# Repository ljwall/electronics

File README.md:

# Electronics

Vague notes on my electronics projects.

## Bootstrapping AVR development

Using a borrowed Arduino UNO to build a version of the [metaboard](https://metalab.at/wiki/Metaboard) prototype board and an ISP.

* [Turn an Arduino UNO into an AVRISP, and make an LED blink](./01_arduino_isp_blink/)
* [Mini-metaboard on a breadboard](./02_mini_meta/)
* [AVRProg on breadboard metaboard](./03_meta_avr_prog/)

## Audio

* [lm386 amplifier](./lm386-amp/)

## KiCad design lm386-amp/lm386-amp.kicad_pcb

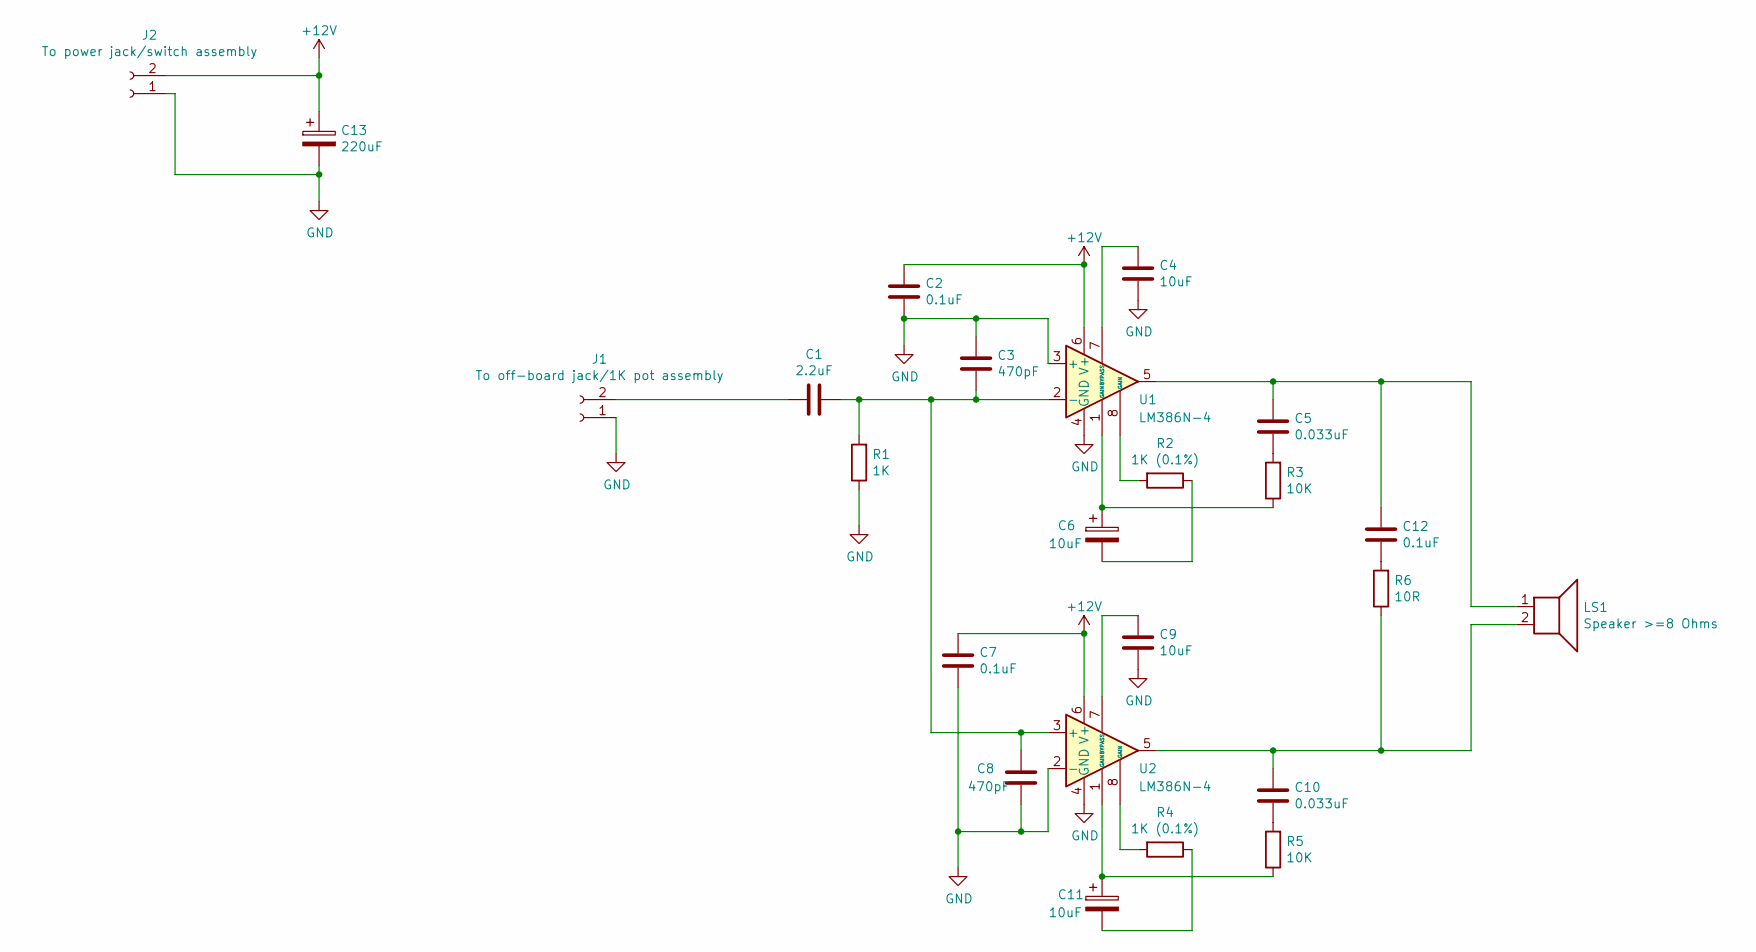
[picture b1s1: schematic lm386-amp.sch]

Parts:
C1: 2.2uF; CP_Radial_D5.0mm_P2.50mm
C2, C7, C12: 0.1uF; C_Disc_D3.4mm_W2.1mm_P2.50mm
C3, C8: 470pF; C_Disc_D3.4mm_W2.1mm_P2.50mm
C4, C6, C9, C11: 10uF; CP_Radial_D6.3mm_P2.50mm
C5, C10: 0.033uF; C_Disc_D4.7mm_W2.5mm_P5.00mm
C13: 220uF; CP_Radial_D8.0mm_P2.50mm
J1: To off-board jack/1K pot assembly; rs-pro-screw-terminal-block-low-prof-P3.5mm-2x1
J2: To power jack/switch assembly; rs-pro-screw-terminal-block-low-prof-P3.5mm-2x1
LS1: Speaker >=8 Ohms; rs-pro-screw-terminal-block-low-prof-P3.5mm-2x1
R1: 1K; R_Axial_DIN0411_L9.9mm_D3.6mm_P12.70mm_Horizontal
R2, R4: 1K (0.1%); R_Axial_DIN0411_L9.9mm_D3.6mm_P12.70mm_Horizontal
R3, R5: 10K; R_Axial_DIN0204_L3.6mm_D1.6mm_P7.62mm_Horizontal
R6: 10R; R_Axial_DIN0204_L3.6mm_D1.6mm_P7.62mm_Horizontal
U1, U2: LM386N-4; DIP-8_W7.62mm_Socket

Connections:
+12V: C2.1, C7.1, C13.1, J2.2, U1.6 (V+), U2.6 (V+)
GND: C2.2, C3.1, C4.2, C7.2, C8.2, C9.2, C13.2, J1.1, J2.1, R1.1, U1.3 (+), U1.4 (GND), U2.2 (-), U2.4 (GND)
unnamed: C1.1, C3.2, C8.1, R1.2, U1.2 (-), U2.3 (+)
unnamed: C1.2, J1.2
unnamed: C4.1, U1.7 (BYPASS)
unnamed: C5.2, R3.2
unnamed: C6.1, R3.1, U1.1 (GAIN)
unnamed: C6.2, R2.1
unnamed: C9.1, U2.7 (BYPASS)
unnamed: C10.1, LS1.2, R6.1, U2.5
unnamed: C10.2, R5.2
unnamed: C11.1, R5.1, U2.1 (GAIN)
unnamed: C11.2, R4.1
unnamed: C5.1, C12.1, LS1.1, U1.5
unnamed: C12.2, R6.2
unnamed: R2.2, U1.8 (GAIN)
unnamed: R4.2, U2.8 (GAIN)

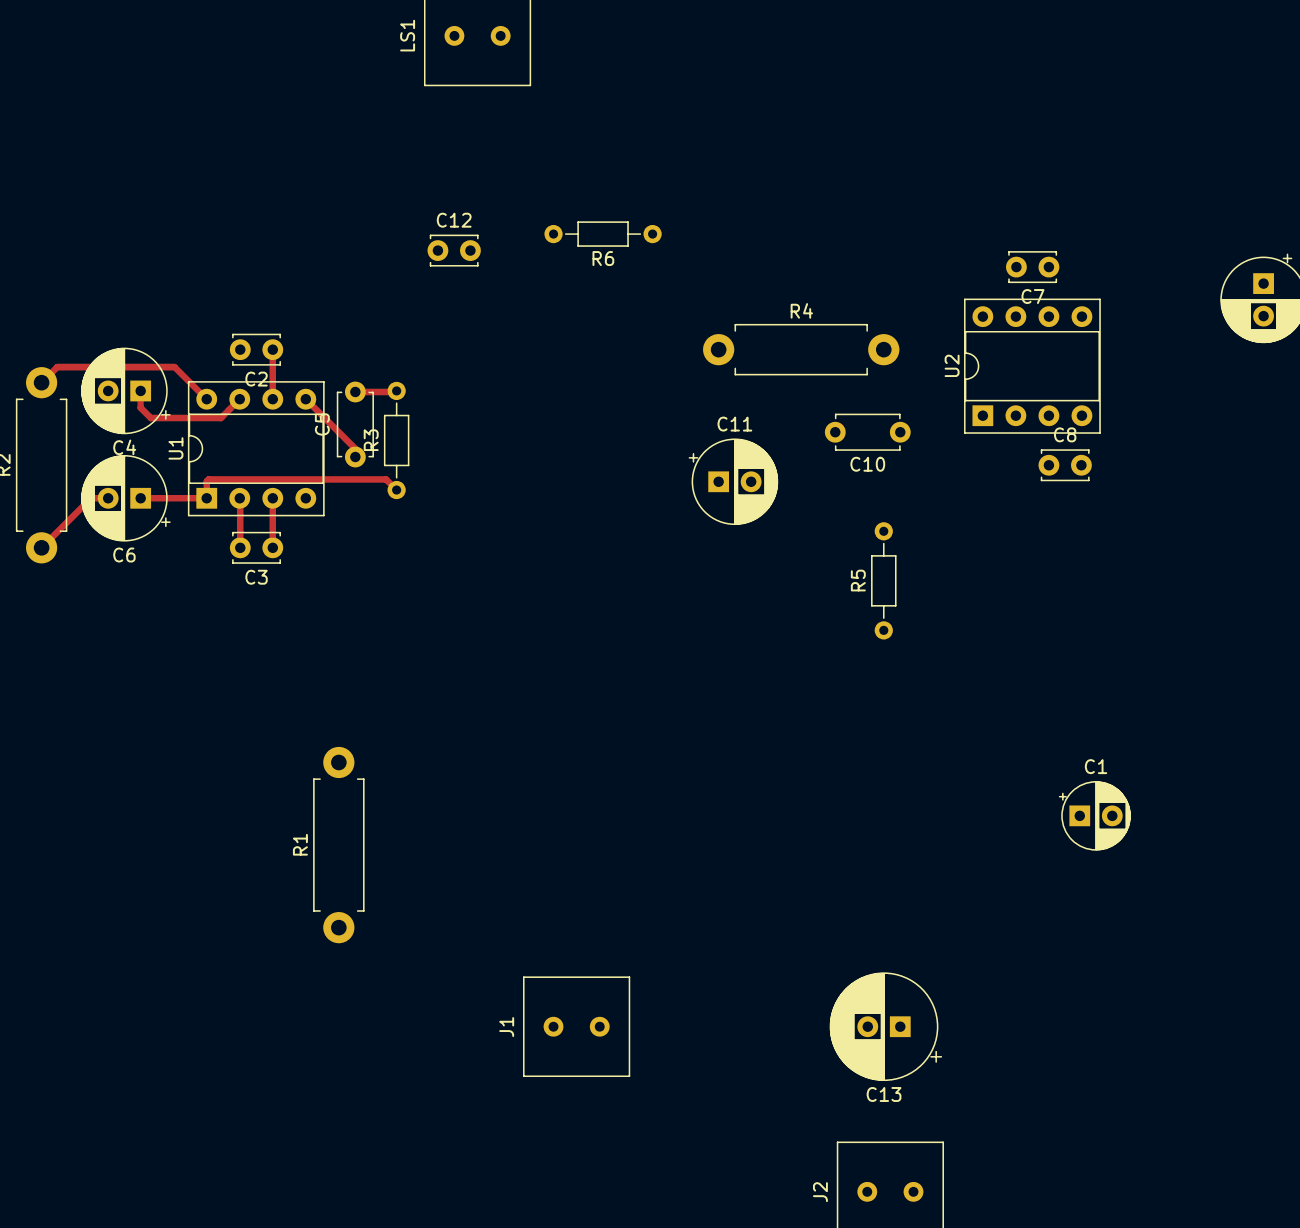
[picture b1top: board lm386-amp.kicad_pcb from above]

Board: 2 copper layers, 24 parts (0 on the bottom side), 17 nets.

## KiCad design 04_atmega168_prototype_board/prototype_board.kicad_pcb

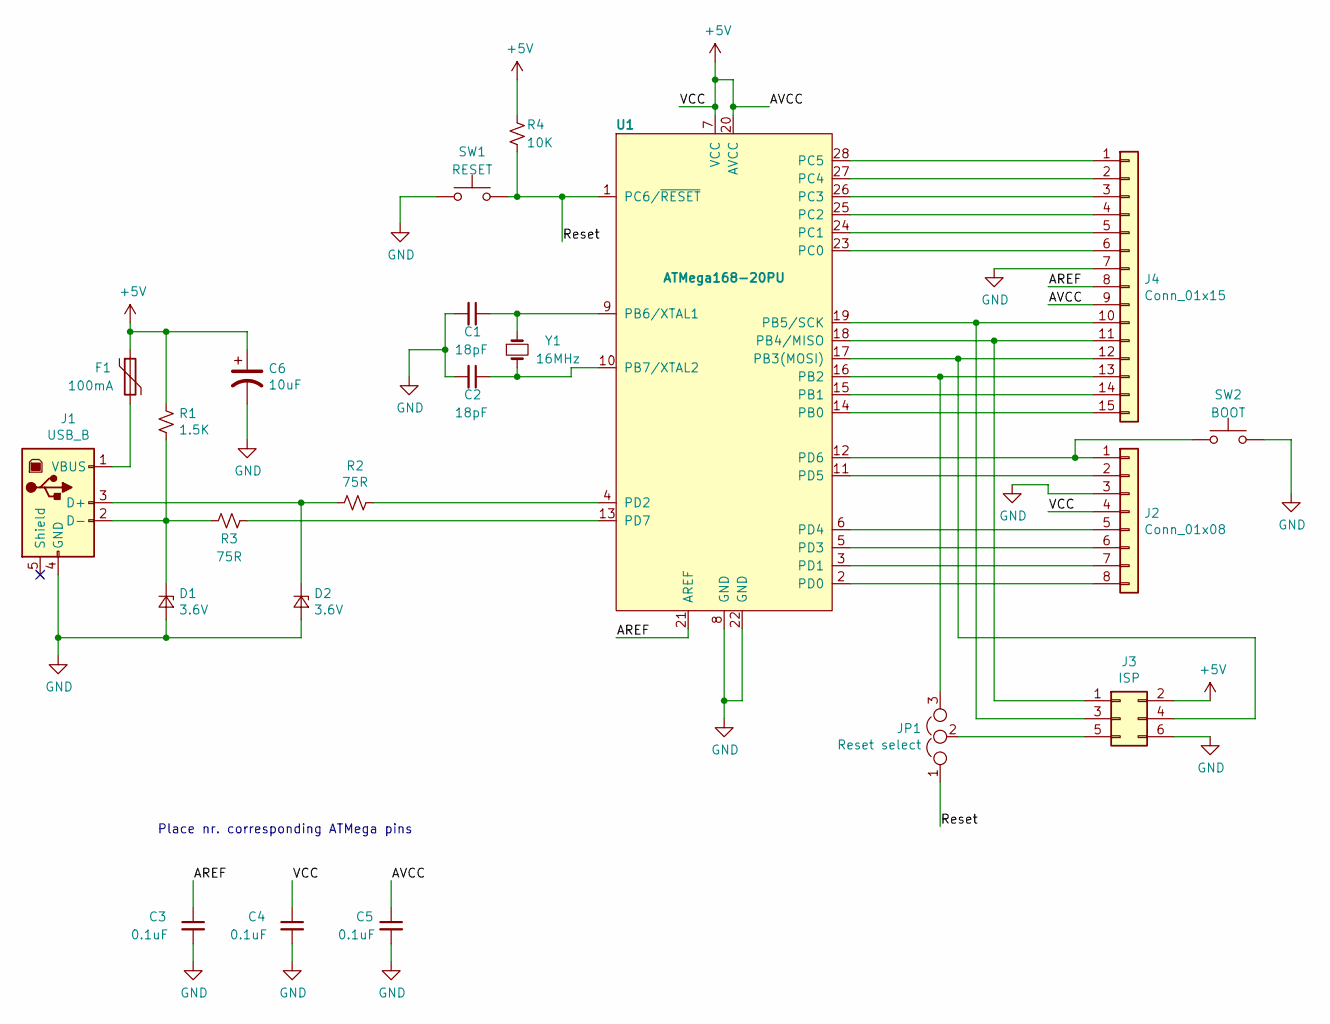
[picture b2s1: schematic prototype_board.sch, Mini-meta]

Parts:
C1, C2: 18pF; C_Disc_D3.0mm_W1.6mm_P2.50mm
C3, C4, C5: 0.1uF; C_Disc_D3.0mm_W1.6mm_P2.50mm
C6: 10uF; CP_Radial_D6.3mm_P2.50mm
D1, D2: 3.6V; D_A-405_P7.62mm_Horizontal
F1: 100mA; Fuse_Littelfuse_395Series
J1: USB_B; USB_B_OST_USB-B1HSxx_Horizontal
J2: Conn_01x08; PinHeader_1x08_P2.54mm_Vertical
J3: ISP; PinHeader_2x03_P2.54mm_Vertical
J4: Conn_01x15; PinHeader_1x15_P2.54mm_Vertical
JP1: Reset select; SolderJumper-3_P1.3mm_Open_Pad1.0x1.5mm
R1: 1.5K; R_Axial_DIN0309_L9.0mm_D3.2mm_P12.70mm_Horizontal
R2, R3: 75R; R_Axial_DIN0204_L3.6mm_D1.6mm_P7.62mm_Horizontal
R4: 10K; R_Axial_DIN0204_L3.6mm_D1.6mm_P5.08mm_Horizontal
SW1: RESET; SW_PUSH_6mm
SW2: BOOT; SW_PUSH_6mm
U1: ATMega168-20PU; DIP-28_W7.62mm
Y1: 16MHz; Crystal_HC49-4H_Vertical

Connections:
+5V: C4.1, C5.1, C6.1, F1.1, J2.4, J3.2, J4.9, R1.1, R4.1, U1.7 (VCC), U1.20 (AVCC)
/AREF: C3.1, J4.8, U1.21 (AREF)
/Reset: JP1.1, R4.2, SW1.2, U1.1 (PC6/~RESET)
GND: C1.2, C2.2, C3.2, C4.2, C5.2, C6.2, D1.2 (A), D2.2 (A), J1.4 (GND), J2.3, J3.6, J4.7, SW1.1, SW2.2, U1.8 (GND), U1.22 (GND)
unnamed: C1.1, U1.9 (PB6/XTAL1), Y1.1
unnamed: C2.1, U1.10 (PB7/XTAL2), Y1.2
unnamed: D1.1 (K), J1.2 (D-), R1.2, R3.2
unnamed: D2.1 (K), J1.3 (D+), R2.2
unnamed: F1.2, J1.1 (VBUS)
unnamed: J2.1, SW2.1, U1.12 (PD6)
unnamed: J2.2, U1.11 (PD5)
unnamed: J2.5, U1.6 (PD4)
unnamed: J2.6, U1.5 (PD3)
unnamed: J2.7, U1.3 (PD1)
unnamed: J2.8, U1.2 (PD0)
unnamed: J3.1, J4.11, U1.18 (PB4/MISO)
unnamed: J3.3, J4.10, U1.19 (PB5/SCK)
unnamed: J3.4, J4.12, U1.17 (PB3(MOSI))
unnamed: J3.5, JP1.2
unnamed: J4.1, U1.28 (PC5)
unnamed: J4.2, U1.27 (PC4)
unnamed: J4.3, U1.26 (PC3)
unnamed: J4.4, U1.25 (PC2)
unnamed: J4.5, U1.24 (PC1)
unnamed: J4.6, U1.23 (PC0)
unnamed: J4.13, JP1.3, U1.16 (PB2)
unnamed: J4.14, U1.15 (PB1)
unnamed: J4.15, U1.14 (PB0)
unnamed: R2.1, U1.4 (PD2)
unnamed: R3.1, U1.13 (PD7)

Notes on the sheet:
Place nr. corresponding ATMega pins

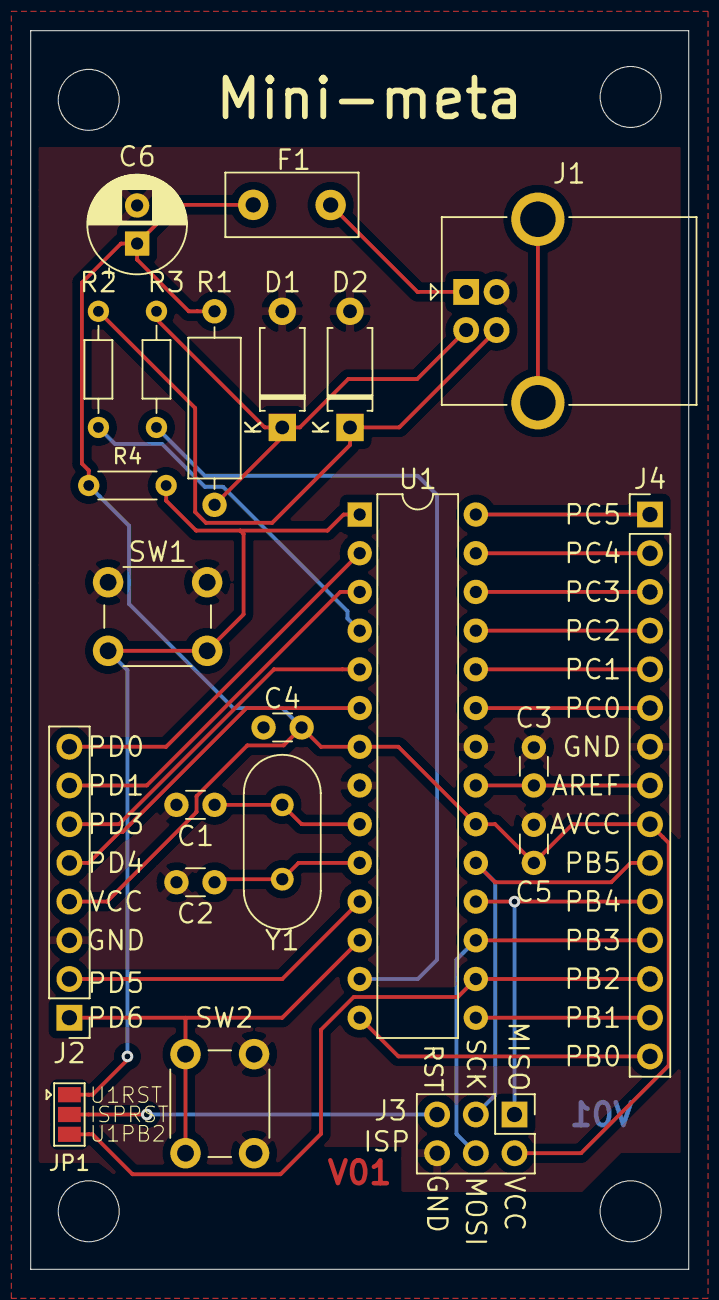
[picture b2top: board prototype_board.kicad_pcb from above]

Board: 2 copper layers, 43.2 x 81.3 mm, 22 parts (0 on the bottom side), 30 nets.

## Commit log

2019-07-07 Initial commit - some READMEs
2019-07-07 Add ArduinoISP sketch
2019-07-07 Add blink on ATTiny44
2019-07-08 Add mini-metaboard breadboard
2019-07-11 Add example of directly programming the ATMega168 with blink via the bootloader
2019-07-15 Add prototype board schematic
2019-07-16 Add mini-amp project
2019-07-22 Add missing "`"
2019-07-22 Add avrprog notes
2019-08-09 Add atmega retoary encoder example
2019-08-09 Add mini-meta atmega168 prototype board kicad project
2019-08-09 Add HD44780 Library for lcd communication
2019-08-10 Update lm386 amp
2019-08-10 Add ATMega168 "Hello, World" lcd code
2019-08-11 LM386 amp, v0
2019-09-15 Add some things that have been hanging around
2021-05-08 MERCY
